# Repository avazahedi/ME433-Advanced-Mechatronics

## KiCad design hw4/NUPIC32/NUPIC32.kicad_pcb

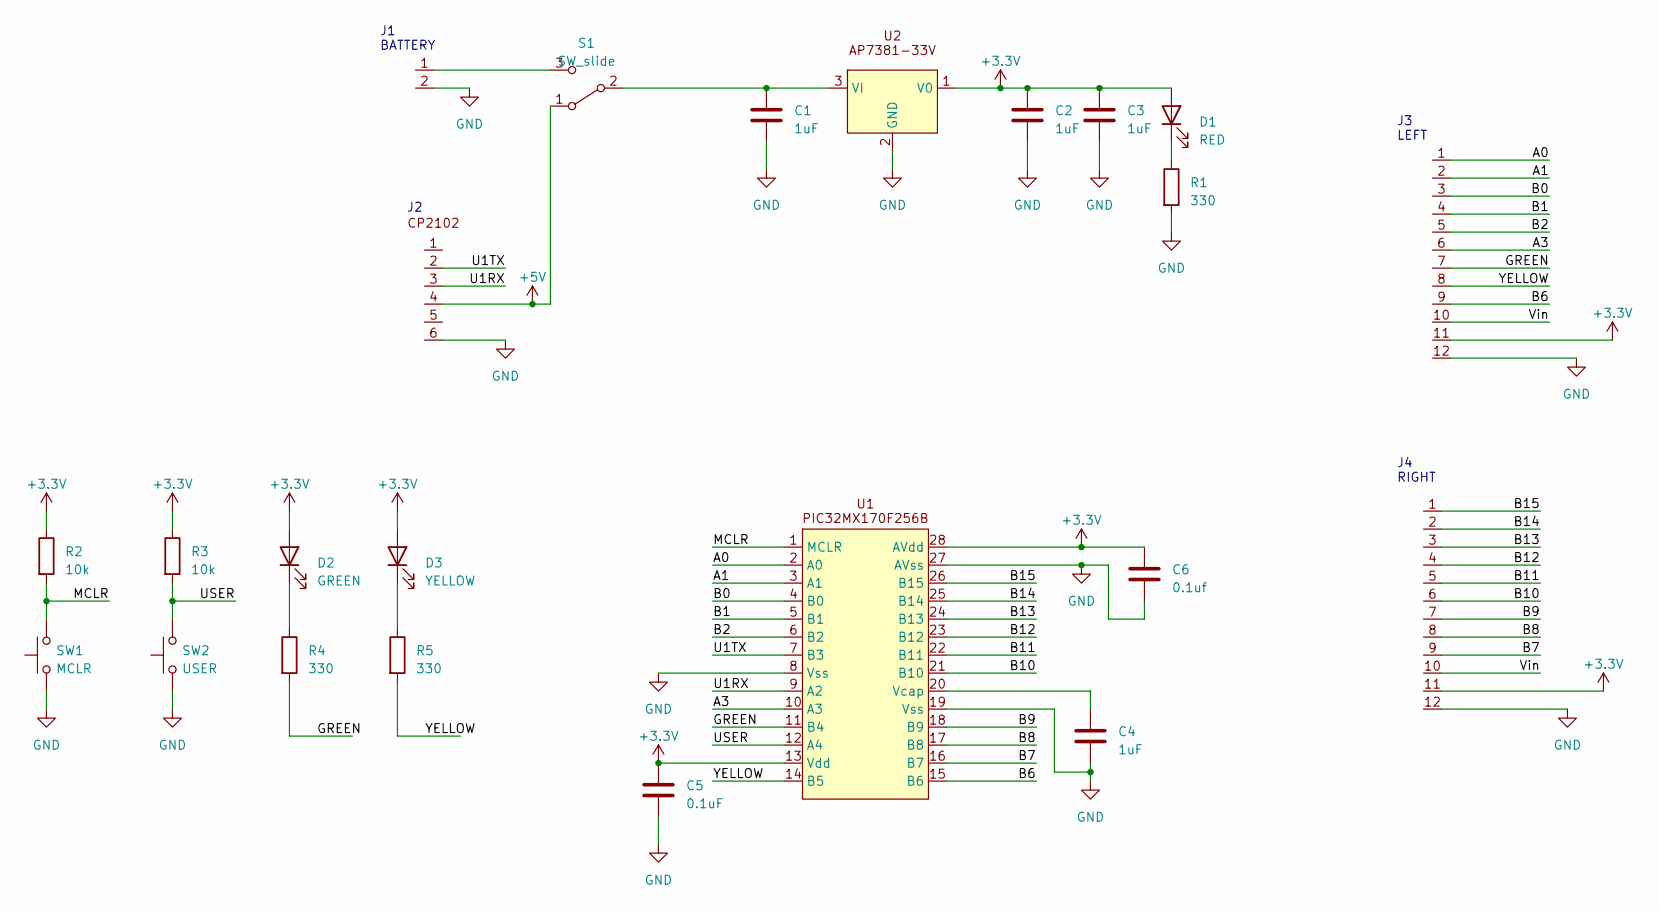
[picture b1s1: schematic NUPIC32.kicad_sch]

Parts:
C1, C2, C3, C4: 1uF; C_Disc_D5.1mm_W3.2mm_P5.00mm
C5: 0.1uF; C_Disc_D3.4mm_W2.1mm_P2.50mm
C6: 0.1uf; C_Disc_D3.4mm_W2.1mm_P2.50mm
D1: RED; LED_D3.0mm
D2: GREEN; LED_D3.0mm
D3: YELLOW; LED_D3.0mm
R1, R4, R5: 330; R_Axial_DIN0207_L6.3mm_D2.5mm_P7.62mm_Horizontal
R2, R3: 10k; R_Axial_DIN0207_L6.3mm_D2.5mm_P7.62mm_Horizontal
S1: SW_slide; slidesw2
SW1: MCLR; pushbutton
SW2: USER; pushbutton
U1: DIP-28_W7.62mm_Socket
U2, U7: PinSocket_1x12_P2.54mm_Vertical
U3: PinSocket_1x06_P2.54mm_Vertical
U4: TO-92L_Inline
U5: PinSocket_1x02_P2.54mm_Vertical

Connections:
+3.3V: C2.1, C3.1, C5.1, C6.1, D1.2 (A), D2.2 (A), D3.2 (A), R2.1, R3.1, U1.13 (Vdd), U1.28 (AVdd), U2.11, U4.1 (V0), U7.11
+5V: S1.1 (A), U3.4
/A0: U1.2 (A0), U7.1
/A1: U1.3 (A1), U7.2
/A3: U1.10 (A3), U7.6
/B0: U1.4 (B0), U7.3
/B1: U1.5 (B1), U7.4
/B2: U1.6 (B2), U7.5
/B6: U1.15 (B6), U7.9
/B7: U1.16 (B7), U2.9
/B8: U1.17 (B8), U2.8
/B9: U1.18 (B9), U2.7
/B10: U1.21 (B10), U2.6
/B11: U1.22 (B11), U2.5
/B12: U1.23 (B12), U2.4
/B13: U1.24 (B13), U2.3
/B14: U1.25 (B14), U2.2
/B15: U1.26 (B15), U2.1
/GREEN: R4.2, U1.11 (B4), U7.7
/MCLR: R2.2, SW1.2, U1.1 (MCLR)
/U1RX: U1.9 (A2), U3.3
/U1TX: U1.7 (B3), U3.2
/USER: R3.2, SW2.2, U1.12 (A4)
/Vin: U2.10, U7.10
/YELLOW: R5.2, U1.14 (B5), U7.8
GND: C1.2, C2.2, C3.2, C4.2, C5.2, C6.2, R1.2, SW1.1, SW2.1, U1.8 (Vss), U1.19 (Vss), U1.27 (AVss), U2.12, U3.6, U4.2 (GND), U5.2, U7.12
unnamed: D1.1 (K), R1.1
unnamed: D2.1 (K), R4.1
unnamed: D3.1 (K), R5.1
unnamed: C1.1, S1.2 (B), U4.3 (VI)
unnamed: S1.3 (C), U5.1
unnamed: C4.1, U1.20 (Vcap)

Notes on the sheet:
J1 BATTERY
J3 LEFT
J4 RIGHT

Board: 2 copper layers, 23 parts (0 on the bottom side), 32 nets, no tracks yet.

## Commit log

2023-04-03 added hw1 and hw2
2023-04-06 fixed hw2 and added hw3
2023-04-21 updated gitignore and added skeleton files
2023-04-21 added hw5 (complete) and skeleton for hw6 and hw7
2023-04-27 got gp7 to blink using i2c
2023-04-27 hw6 done
2023-04-27 hw5 pics
2023-04-27 cleaned up repo
2023-04-27 cleaned up hw6 code
2023-04-27 hw 7 done
2023-04-28 fixed write statement to correctly show whoami() value
2023-05-03 hw8 oled + accelerometer data
2023-05-03 hw9 filtering
2023-05-09 Added HW4 files. Does not include routing for board because we were not provided header distances. Will add later if provided.
2023-05-09 started hw10. Can turn on Neopixel LEDs and set to different RGB values. r and g are flipped for unknown reason
2023-05-09 static rainbow
2023-05-09 moving rainbow on neopixel
2023-05-16 hw11
2023-05-29 added cad files for hw12
2023-06-04 hw13
2023-06-08 hw14 servo motor control
